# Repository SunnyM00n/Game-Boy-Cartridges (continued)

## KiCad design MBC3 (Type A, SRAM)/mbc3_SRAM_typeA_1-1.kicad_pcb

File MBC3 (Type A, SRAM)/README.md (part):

# Game Boy MBC3 Cartridge - Type A, SRAM

This is an updated design of my flashable MBC3-based cartridge for the Game Boy. The MBC3 mapper improves a lot over the MBC1, and includes a real-time clock for everyone's favorite battery-sucking game.... Mary Kate and Ashley Pocket Planner! Oh, and Pokemon.

**This MBC3 cartridge uses brand new M29F160 EEPROM chips and battery-backed SRAM.**

This circuit board should cover most, if not all, MBC3 games. The features are as follows:

- Able to make games up to 2 MB in size, that use up to 256 Kbit of RAM
- Compatibility with all four of the popular Game Boy battery management ICs - MM1026, MM1134, BA6129, and BA6735
- The option to add battery backup to the cartridge *without* the need of the original battery management ICs
- Fully compatible with both the <a href="https://www.gbxcart.com/">GBxCart RW</a> and sanni's <a href="https://github.com/sanni/cartreader">Open Source Cart Reader (OSCR)</a> so you can transfer games and save files to and from the board

All gerbers and source files can be found in this repo, as this project is fully open source.

## Important Things Before You Start

1) To use this board, you need to have an original Game Boy game that uses an MBC3 mapper chip. <a href="https://catskull.net/gb-rom-database/">You can find a list of games and their mappers here</a>. Use the search function. Please note the RAM is in bytes, not bits. Since SRAM in this repo is defined in bits, you need to convert by multiplying the number of bytes by 8.
2) You will need to remove the MBC3 from your donor cartridge for use on this board. This will require a hot air rework station or a hot plate. There's a list below of other parts you can re-use from the donor cartridge.
3) When soldering parts on, it's a good idea to put kapton tape or otherwise cover the bottom cartridge edge. You do not want to get solder on the cartridge contacts.
4) I am not responsible for any damage you do to your self or your property. Attempt this project at your own risk.
5) I do not guarantee design compatibility. You may encounter issues with certain games. There is also a chance I have made an error in the design or the BOM - if this is the case, I will do everything I can to address the problem as quickly as possible.
6) If you are using this board to make games other than for personal use, you must have permission from the originator to use and distribute any ROM images or other related material. You are responsible for making sure you adhere to any license requirements.

DO NOT use my circuit boards for profiting from stolen work - this especially includes homebrew content, ROM hacks, and using fan-made labels without permission from the originator. **Support original creators!**

## Board Characteristics and Order Information

The zipped folder contains all the gerber files for this board. The following options **must** be chosen when ordering boards for yourself.

- Thickness: 0.8mm
- Surface Finish: ENIG
- Gold Fingers: Yes, 30° chamfer

**I sell this blank circuit board on Etsy, so you don't have to buy a bunch of multiples if you don't want to.** (Click the banner!)

You can use the zipped folder at any board fabricator you like. You may also buy the board from PCBWay using this link (disclosure: I receive 10% of the sale value to go twoards future PCB orders of my own):

<a href="https://oshpark.com/shared_projects/ahA0HcIn">The board is also listed on OSH Park as well.</a> **Be sure to get them in 0.8mm thickness if you order from here.**

## Required Equipment

The EEPROM on the board needs to be programmed somehow. There are a few options for doing this:

1) <a href="https://www.gbxcart.com/">**GBxCart**</a>. This is a perfect option if you want an easy way to make Game Boy cartridges without a lot of extra effort. This is a standalone flasher that plugs into your computer via USB. The cartridge circuit board is fully compatible with it, and it makes reflashing games extremely easy using <a href="https://github.com/lesserkuma/FlashGBX">lesserkuma's FlashGBX software</a>.
2) <a href="https://github.com/sanni/cartreader">**OSCR**</a> by sanni. This is the Open Source Cart Reader, capable of making backups of both the ROM and RAM contents of cartridges across many different systems - like the NES, SNES, Genesis, and of course Game Boy and Game Boy Advance. And you can also use it to flash these Game Boy cartridges. The OSCR however requires assembly (or someone to assemble it for you) and is a bit more cumbersome to interface with on a PC, but it's an extremely powerful tool that I can't recommend enough if you want to expand past Game Boys.
3) At the lowest level, you can buy an EEPROM programmer with a TSOP chip programming adapter. The downside to this method is that you have to desolder the chip every time you want to program it. The <a href="https://flashcatusb.com/">FlashcatUSB</a> is one popular option in retro spaces, but I use the <a href="https://xgecu.myshopify.com/products/xgecu-new-t48-tl866-3gprogrammer-v12-01-support-28000-ics-for-spi-nor-nand-flash-emmc-bga153-162-169-100-221-tsop-sop-plcc">T48 programmer</a> with the <a href="https://xgecu.myshopify.com/products/100-original-xgecu-adp_f48_ex-1-tsop48-special-adapter-for-nor-flash-only-use-on-t48-tl866-3g-programmer">TSOP48 adapter</a>.

## Battery Safety

When assembling a board, I recommend populating all the parts *except* the battery, and getting it to run initially without it. This is to make it easier to fix any solder connections that might need fixing, without having to worry about getting the battery hot. And if you need to rework anything near the battery after you've put it on the board, be safe and remove it before putting a hot soldering iron next to it.

If you're assembling these boards with a hot plate or hot air, *do not* solder the battery on this way. You should use an iron, and keep heat off of the battery as much as possible. 

(Also check polarity!)

## Board Configurations

The board comes with five sets of jumper pads for solder bridges. SJ3, SJ5, and SJ6 require you to solder bridge the middle pad either to the left or right pads. SJ1 and SJ4 are configured by either leaving them alone or bridging them with solder. Here are the situations where you need to add solder bridges.

**<a href="https://github.com/MouseBiteLabs/Game-Boy-Cartridges/wiki/MBC3">You can check out the wiki for some pictures of boards in various configurations to follow along with.</a>**

### Making Games Without SRAM or Battery (SJ1 and SJ4)

Solder bridge SJ1 and SJ4 if your game does not use any SRAM or battery. I don't believe there were ever any MBC3 games made *without* SRAM, but if you wanted to... remove it for some reason, you can.

### MBC3 Type Select (SJ3)

The MBC3 chip you use from the donor cartridge can be one of a few different types:

- If your MBC3 doesn't have a revision letter on it (it just says "MBC3" on it) then bridge the middle pad of SJ3 to the left. (You will also need to populate Q1!)
- If your MBC3 *does* have a revision letter, such as MBC3A or MBC3B, then bridge the middle pad of SJ3 to the right.

*[Images of MBC3 chips from <a href="https://gbhwdb.gekkio.fi/cartridges/mbc3.html">Game Boy Hardware Database</a>.]*

### RAM Size Selection (SJ5 and SJ6, or SW1)

These jumpers are located underneath the MBC3 chip, and labeled "64K" and "256K". Solder them to configure the amount of RAM your cart uses. You must configure these pads for every game you make, unless you do not need RAM. <a href="https://catskull.net/gb-rom-database/">You can find a list of games here with their respective RAM sizes.</a>

- If the game you're making uses 256 Kbit of RAM, then solder the middle pads of the two jumper sets to the right pads.
- If the game you're making uses 64 Kbit of RAM, then solder the middle pads of the two jumper sets to the left pads.
- SJ5 and SJ6 must be soldered in the same direction.
- The footprint of these selection pads should allow for a DPDT switch, part number CAS-220A1, to be placed on these pads instead of having to bridge the pads with solder.

Note that you can make games that only require 64 Kbit of RAM and still use a 256 Kbit SRAM chip. You still need to configure the jumpers to the 64 Kbit setting, though.

### Games Without a Real-Time Clock

If your game does *not* use the RTC function with the crystal X1, then you need to bridge the pads of Z1.

## Test Points and Final Checkout

On the back of the board are five test points. Here's where they are connected:

- TP1: SRAM supply voltage
- TP2: Battery voltage (after R1)
- TP3: Battery voltage (positive terminal of battery)
- TP4: Ground
- TP5: VCC input voltage

After you assemble your game, you should measure the current out of the battery. But first, you should program it with the GBxCart, or if you programmed the EEPROM separately, put it into a Game Boy and cycle power once. Then, flip the PCB upside down on a non-conductive surface (not your leg), and set your multimeter in DC millivolts (or volts). Put the positive probe on TP3 and the negative probe on TP2. If you used a 10kΩ for R1, as indicated in the BOM, you should read a voltage in the single or tens of millivolts for non-RTC games, or up to 40 mV for games using a real-time clock. If you have something much higher, especially voltages above 40mV, then you likely have an issue or short circuit on the board somewhere.

**Note: You need to power up the game at least once before battery currents will make sense - the battery management ICs can start up in an unknown state before applying main power to the board.**

To estimate battery life, see <a href="https://github.com/MouseBiteLabs/Game-Boy-MBC3-Cartridge/tree/main/Technical#estimating-battery-life">this section in the Technical Design Document of my first MBC3 board design</a>, or for more in-depth analysis, <a href="https://hackaday.io/project/11864-tritiled/log/72554-determining-maximum-runtime-176-to-202-years-cr2032">this Hackaday post</a>.

### Current Draw Measurements

The revision of MBC3 chip you are using will influence the current draw out of the battery when the game is off, and thus how long your battery life will last. Using the real-time clock function on the MBC3 will draw more current than if you do not.

For the test set up, I am replacing the battery with a regulated DC power supply set for 3 VDC for consistency, on a cart board with an MM1134 chip for U4, and brand new AS6C62256 SRAM. The "no RTC" measurements have Z1 (or C3) shorted, and the "with RTC" measurements have R2, C2, Z1, and X1 populated. I am using a Fluke 117 Multimeter in DC mV mode for measurements.

| Rev   | P/N      | Current draw (without RTC) | Battery Life Estimate (no RTC, CR2025) | Current draw (with RTC) | Battery Life Estimate (RTC, CR2025)  | Battery Life Estimate (RTC, CR2032) |
| ----- | -------- | -------------------------- | -------------------------------------- | ----------------------- | ------------------------------------ | ----------------------------------- |
| MBC3  | LR385364 |          0.2 uA            |               >50 years                |            1.8 uA       |               10 years               |            14 years                 |
| MBC3  | BU3631K  |          0.6 uA            |                31 years                |            1.6 uA       |               12 years               |            16 years                 |
| MBC3  | P-1      |          0.4 uA            |                47 years                |            3.8 uA       |               5 years                |             7 years                 |
| MBC3A | LR38536B |          0.2 uA            |               >50 years                |            1.5 uA       |               13 years               |            18 years                 |
| MBC3A | BU3632K  |          0.5 uA            |                37 years                |            1.5 uA       |               13 years               |            18 years                 |
| MBC3A | P-2      |          0.5 uA            |                37 years                |            3.9 uA       |               5 years                |            7 years                  |
| MBC3B | BU3634K  |          0.6 uA            |                31 years                |            1.5 uA       |               13 years               |            18 years                 |
| MBC3B | P-2      |          0.4 uA            |                47 years                |            3.7 uA       |               5 years                |            7 years                  |

*Note: The SRAM I used, AS6C62256, drew 0.05 uA by itself for these tests. Your current draw may vary depending on the SRAM you are using.*

## Board Fitment

The shape of this board was originally meant to mimic original Game Boy circuit boards as closely as possible. Unfortunately, when placed in some aftermarket Game Boy cartridge shells (like those from Cloud Game Store), the circuit board has a lot of freedom to rotate around the main screw hole in the bottom-middle of the cartridge. This can cause misalignment when you put it in a Game Boy, which can cause a game to either not load properly (garbled Game Boy logo) or shut off the Game Boy because of a short circuit. This isn't *dangerous* or anything, just annoying.

In order to make the boards fit nicer in any kind of shell, I added extended tabs of circuit board material to the edges of the cartridges to keep it from rotating too much in shells, which was suggested to me by <a href="https://github.com/orangeglo">orangeglo</a>! (Thanks!)

If you're having trouble fitting the circuit board into a shell, because the tabs interfere with the cart edges, you can safely sand or trim them down as there is no copper within the tabs themselves. The only shell that appears to require any kind of trimming are Kitsch-Bent shells.

## Bill of Materials (BOM)

Your parts list will vary depending on the game you are trying to make, and what chips you have for the battery management (if any). **You cannot use both U4 and U5 - you must choose one or the other.** U4 comes from a donor cartridge, and U5 is a readily available aftermarket option.

Please carefully review the parts you need for the board you are trying to make. Do not add any parts to your build that don't appear in the column for the game you are making. This means you *cannot* populate every component on the board at the same time.

**NOTE: If you are *not* using the RTC function of the MBC3, you need to bridge the pads of Z1 (or C3) with solder.**

| Reference Designators | Value/Part Number              | Package          | Description        | No save carts | Save carts with U4 | Save carts without U4 | Source                                           |
| --------------------- | ------------------------------ | ---------------- | ------------------ | ------------- | ------------------ | --------------------- | ------------------------------------------------ |
| B1                    | CR2032, CR2025, CR2016         | CR2032           | Backup Battery     |               | x                  | x                     | [https://mou.sr/3SeAzfT](https://mou.sr/3SeAzfT) |
| C1                    | 0.1uF                          | 0603             | Capacitor (MLCC)   | x             | x                  | x                     | [https://mou.sr/3ENc15O](https://mou.sr/3ENc15O) |
| C2                    | 15pF                           | 0603             | Capacitor (MLCC)   |               | If using RTC       | If using RTC          | https://mou.sr/3PPorjO                           |
| Z1                    | 15pF                           | 0603             | Capacitor (MLCC)   |               | If using RTC       | If using RTC          | https://mou.sr/3PPorjO                           |
| C4                    | 0.1uF                          | 0603             | Capacitor (MLCC)   |               | x                  |                       | [https://mou.sr/3ENc15O](https://mou.sr/3ENc15O) |
| C5                    | 0.1uF                          | 0603             | Capacitor (MLCC)   |               | x                  | x                     | [https://mou.sr/3ENc15O](https://mou.sr/3ENc15O) |
| C6                    | 10uF                           | 0603             | Capacitor (MLCC)   |               | x                  | x                     | [https://mou.sr/3mZtSkF](https://mou.sr/3mZtSkF) |
| C7                    | 0.1uF                          | 0603             | Capacitor (MLCC)   | x             | x                  | x                     | [https://mou.sr/3ENc15O](https://mou.sr/3ENc15O) |
| C8                    | 0.1uF                          | 0603             | Capacitor (MLCC)   |               |                    | x                     | [https://mou.sr/3ENc15O](https://mou.sr/3ENc15O) |
| Q1                    | 2N7002                         | SOT-23           | N-Channel FET      |               | If MBC3 no rev     | x                     | [https://mou.sr/3rgfh6J](https://mou.sr/3rgfh6J) |
| R1                    | 10k                            | 0603             | Resistor           |               | x                  | x                     | [https://mou.sr/3riR7IH](https://mou.sr/3riR7IH) |
| R2                    | 330k                           | 0603             | Resistor           |               | If using RTC       | If using RTC          | [https://mou.sr/3PZ2pvj](https://mou.sr/3PZ2pvj) |
| R9                    | 130k                           | 0603             | Resistor           |               |                    | x                     | [https://mou.sr/3MjXliy](https://mou.sr/3MjXliy) |
| R10                   | 49.9k                          | 0603             | Resistor           |               |                    | x                     | https://mou.sr/3Q3NRZO                           |
| U1                    | M29F160                        | TSOP-48          | Flash EEPROM       | x             | x                  | x                     | [https://mou.sr/3N0a9eL](https://mou.sr/3N0a9eL) |
| U2                    | MBC3                           | QFP-32           | MBC3 Mapper        | x             | x                  | x                     | Donor MBC3 Game Boy cartridge                    |
| U3                    | AS6C6264, AS6C62256            | SOP-28           | SRAM               |               | x                  | x                     | [https://mou.sr/450klcY](https://mou.sr/450klcY) |
| U4                    | MM1026, MM1134, BA6129, BA6735 | SOIC-8           | Battery Management |               | x                  |                       | Donor Game Boy cartridge                         |
| U5                    | TPS3613                        | MSOP-10          | Battery Management |               |                    | x                     | [https://mou.sr/45Ir2kh](https://mou.sr/45Ir2kh) |
| X1                    | 32.768 kHz                     | Radial           | Crystal Oscillator |               | If using RTC       | If using RTC          | https://mou.sr/3ZteKuy                           |

*Note that C9 - C11 footprints are only included on the board for strange edge cases that may require them sometime in the future; do not populate! See the technical design document for more information.*

### Usable Donor Cartridge Parts

You can use a few parts from the donor cart on the new board to save some money. Note that you will generally get better reliability with new parts as opposed to old ones. For example: I have seen failed RAM chips from donors in the past.

1) **C1/Z1, C2, R2, X1: RTC Components** - You can move over these parts if you're using the real-time clock function. The two capacitors are the same value, so they are interchangeable. On games that *don't* use the RTC, you can't move "Z1" over, because it's a resistor on those boards. Also be careful that on my board, the RTC capacitors are designated as "Z1" and "C2" - don't accidentally move the wrong capacitors over from the donor board to these spots!
2) **U2: MBC3** - This one is required
3) **U3: SRAM** - You can use this part *only if* the game you're making uses the same or less amount of RAM that the donor cartridge does
4) **U4: Battery Management IC** - Using this is probably preferred over the TPS3613 because it'll save you money and parts to put on

You could probably transfer over most of the 0.1uF capacitors but they're pretty cheap anyway, so I generally just recommend buying new resistors and capacitors.

## Things to Remember

- The footprint for the battery can fit a CR2032, CR2025, or CR2016 with solder tabs. The only difference is the mAh capacity (larger number = longer life). If you get Panasonic tabbed batteries, you may have to trim the battery tabs to make them fit on the footprint.
  - For untabbed coin cells, you can find battery retainer adapters online, <a href="https://retrogamerepairshop.com/products/hdr-game-boy-game-battery-retainer?variant=40511013290156">like this one</a>.
- For battery management, use either U4 *or* U5 and supporting components. **Do not** use U4 and U5 simultaneously on one board. They will interfere with each other.
- Generally, ROM sizes are conveyed in terms of kilo**bytes** and mega**bytes** (KB, MB). RAM size is usually conveyed in terms of kilo**bits** or mega**bits** (Kbit, Mbit). You can convert Kbit and Mbit to KB and MB by dividing Kbit or Mbit by 8. For example, 256 Kbit = 32 KB.
- You only need to provide ROM and RAM chips that have at least *or greater* the size of the game you are trying to make. That means you can use a 256 Kbit SRAM chip for a game that only requires 64 Kbit of RAM!

## Labels

If you want a Bucket Mouse branded label for your cartridge, look no further than <a href="https://krizdingus.com/mousebitelabs/">krizdingus's designs</a>. Special thanks to Kris for designing these, they look awesome! (If you are going to order/print these, use the high-res images hosted on his website, and *keep the labels for personal or non-commercial use only.*)

## Why Not FRAM?

This particular board is designed for using low retention power SRAM, or Static RAM. One downside to SRAM is that you need a battery to keep the SRAM powered on even when the game is turned off if you want to retain the data on the chip. So eventually the battery will die, and your save data will be lost.

The other popular option for holding save data is using FRAM, or Ferroelectric RAM, to keep save data around even after the battery dies (specifically, the popular part that's used for Game Boy FRAM carts is the FM18W08).

So, why would anyone ever use SRAM over FRAM if FRAM doesn't need a battery? Well, they do come with a number of downsides:

1) Quality, new stock, 5V tolerant FRAM is expensive ($12+ per part at the time of writing).
2) Cheaper FRAM chips from eBay or Aliexpress are notoriously flaky (anecdotally, ~50% success rate).
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
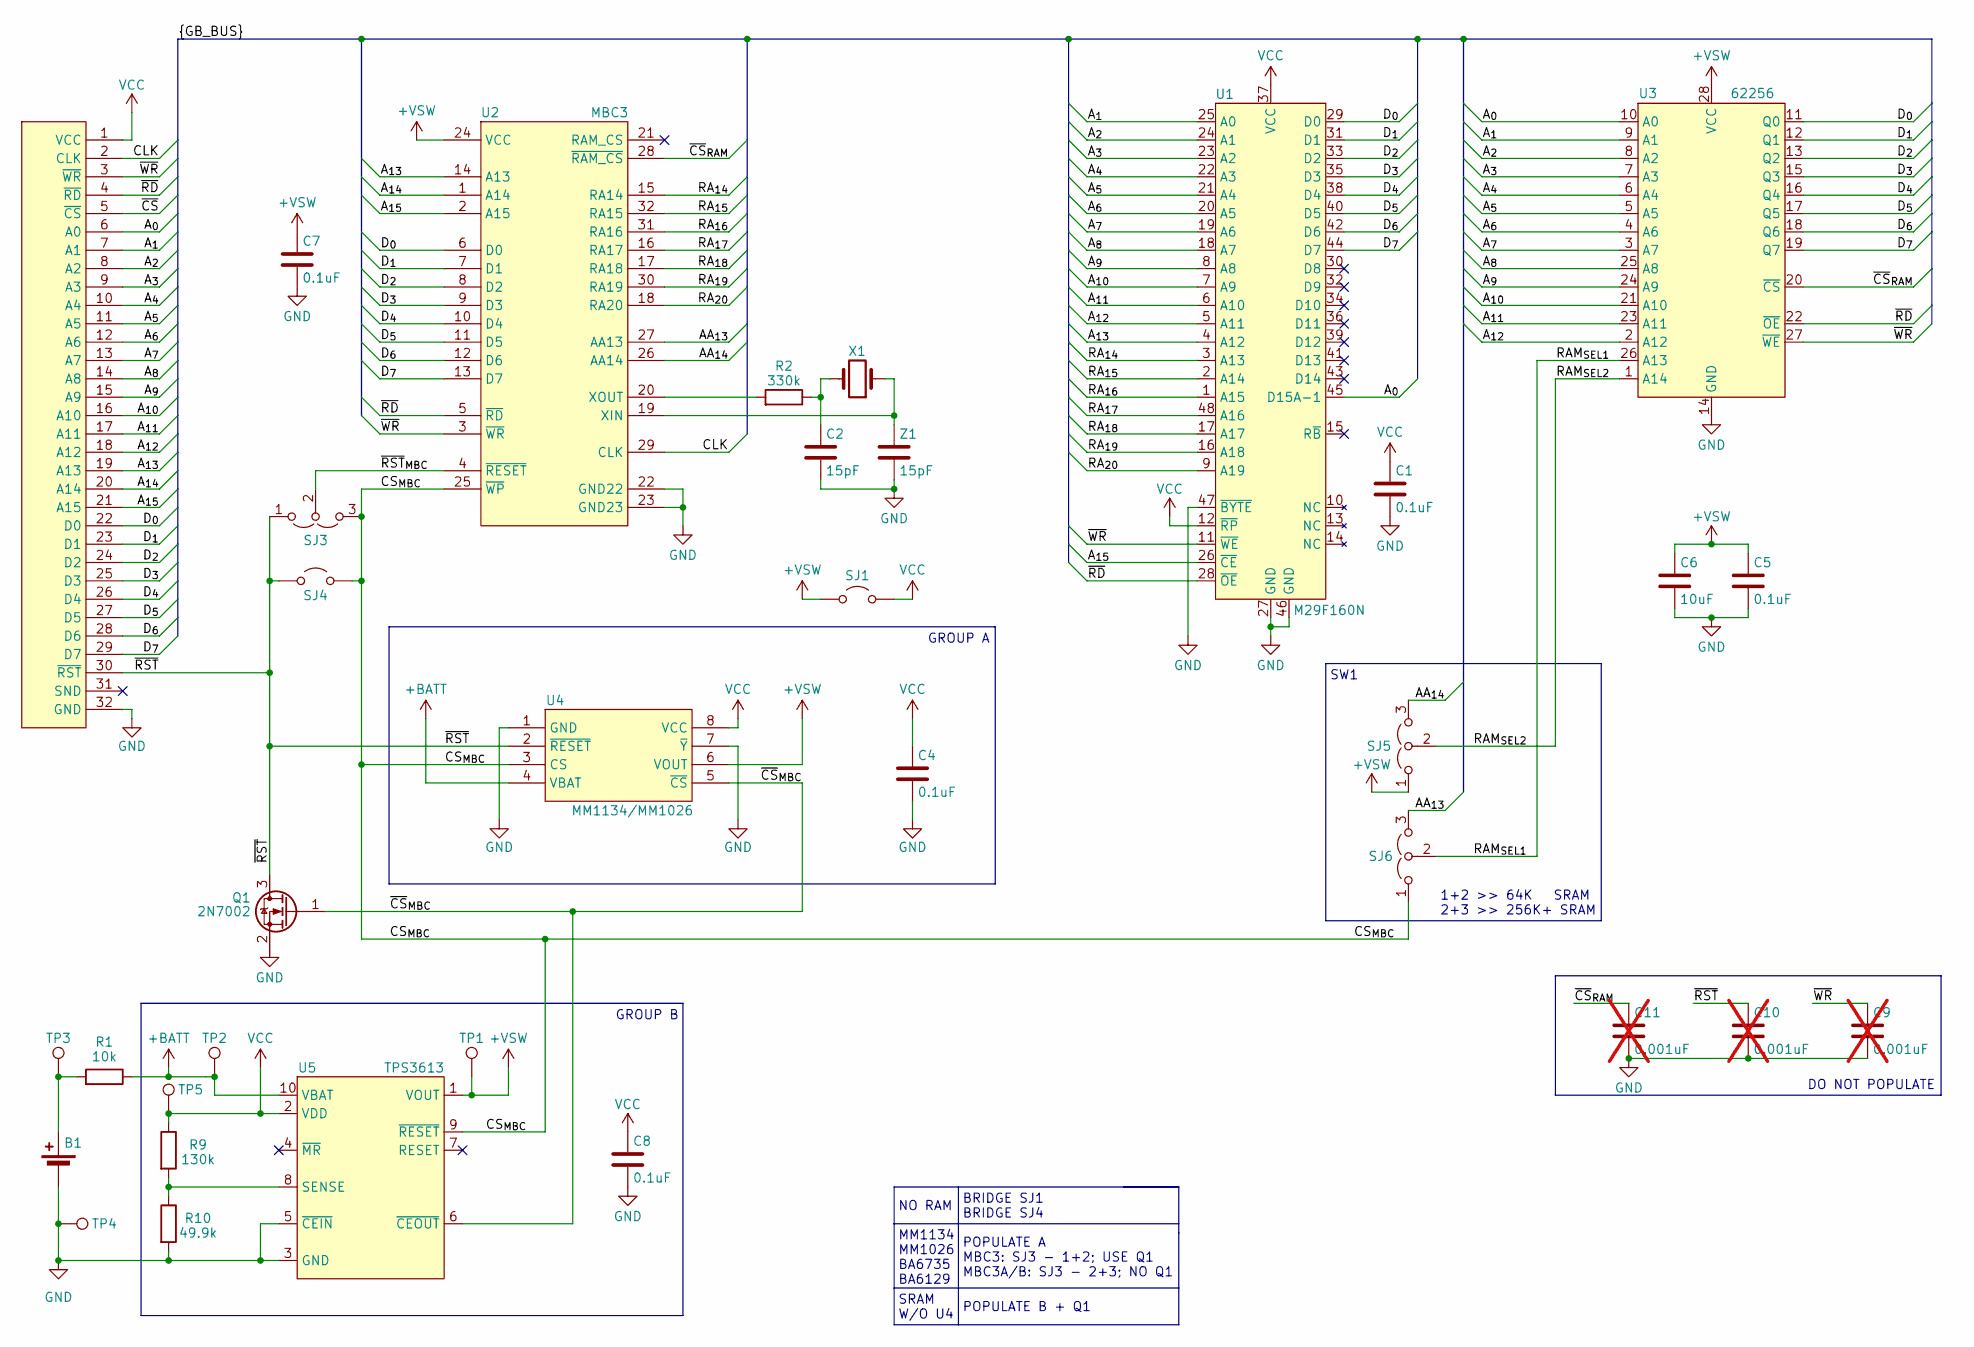
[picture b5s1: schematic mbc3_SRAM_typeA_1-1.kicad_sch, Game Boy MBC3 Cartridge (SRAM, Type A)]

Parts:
B1: CR2025
C1, C4, C5, C7, C8: 0.1uF; C_0603_1608Metric_Boxed
C2: 15pF; C_0603_1608Metric_Boxed
C6: 10uF; C_0603_1608Metric_Boxed
C9, C10, C11: 0.001uF; C_0603_1608Metric_Boxed; not fitted
P2: GBC_CARTTAB; GBC_CART_TABBED
Q1: 2N7002; SOT-23
R1: 10k; R_0603_1608Metric_Boxed
R2: 330k; R_0603_1608Metric_Boxed
R9: 130k; R_0603_1608Metric_Boxed
R10: 49.9k; R_0603_1608Metric_Boxed
SJ1, SJ4: SJ
SJ3, SJ5, SJ6: SJ2W; SJ_2
TP1, TP2, TP3, TP4, TP5: TPB1,27; TestPoint_Pad_D1.0mm
U1: M29F160N; TSOP-I-48_18.4x12mm_P0.5mm
U2: MBC3; QFP-32
U3: 62256; SO28
U4: MM1134/MM1026; SOIC-8_3.9x4.9mm_P1.27mm
U5: TPS3613; MSOP-10_3x3mm_P0.5mm
X1: XTAL-3.2X1.5; XTAL3215
Z1: 15pF; C_0603_1608Metric_Boxed

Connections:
+BATT: R1.1, TP2.1, U4.4 (VBAT), U5.10 (VBAT)
+VSW: C5.1, C6.1, C7.1, SJ1.2 (B), SJ5.1 (A), TP1.1, U2.24 (VCC), U3.28 (VCC), U4.6 (VOUT), U5.1 (VOUT)
/AA_{13}: SJ6.3 (B), U2.27 (AA13)
/AA_{14}: SJ5.3 (B), U2.26 (AA14)
/A_{0}: P2.6 (A0), U1.45 (D15A-1), U3.10 (A0)
/A_{1}: P2.7 (A1), U1.25 (A0), U3.9 (A1)
/A_{2}: P2.8 (A2), U1.24 (A1), U3.8 (A2)
/A_{3}: P2.9 (A3), U1.23 (A2), U3.7 (A3)
/A_{4}: P2.10 (A4), U1.22 (A3), U3.6 (A4)
/A_{5}: P2.11 (A5), U1.21 (A4), U3.5 (A5)
/A_{6}: P2.12 (A6), U1.20 (A5), U3.4 (A6)
/A_{7}: P2.13 (A7), U1.19 (A6), U3.3 (A7)
/A_{8}: P2.14 (A8), U1.18 (A7), U3.25 (A8)
/A_{9}: P2.15 (A9), U1.8 (A8), U3.24 (A9)
/A_{10}: P2.16 (A10), U1.7 (A9), U3.21 (A10)
/A_{11}: P2.17 (A11), U1.6 (A10), U3.23 (A11)
/A_{12}: P2.18 (A12), U1.5 (A11), U3.2 (A12)
/A_{13}: P2.19 (A13), U1.4 (A12), U2.14 (A13)
/A_{14}: P2.20 (A14), U2.1 (A14)
/A_{15}: P2.21 (A15), U1.26 (~CE), U2.2 (A15)
/CLK: P2.2 (CLK), U2.29 (CLK)
/CS_{MBC}: SJ3.3 (B), SJ4.2 (B), SJ6.1 (A), U2.25 (~WP), U4.3 (CS), U5.9 (~RESET)
/D_{0}: P2.22 (D0), U1.29 (D0), U2.6 (D0), U3.11 (Q0)
/D_{1}: P2.23 (D1), U1.31 (D1), U2.7 (D1), U3.12 (Q1)
/D_{2}: P2.24 (D2), U1.33 (D2), U2.8 (D2), U3.13 (Q2)
/D_{3}: P2.25 (D3), U1.35 (D3), U2.9 (D3), U3.15 (Q3)
/D_{4}: P2.26 (D4), U1.38 (D4), U2.10 (D4), U3.16 (Q4)
/D_{5}: P2.27 (D5), U1.40 (D5), U2.11 (D5), U3.17 (Q5)
/D_{6}: P2.28 (D6), U1.42 (D6), U2.12 (D6), U3.18 (Q6)
/D_{7}: P2.29 (D7), U1.44 (D7), U2.13 (D7), U3.19 (Q7)
/RAM_{SEL1}: SJ6.2 (C), U3.26 (A13)
/RAM_{SEL2}: SJ5.2 (C), U3.1 (A14)
/RA_{14}: U1.3 (A13), U2.15 (RA14)
/RA_{15}: U1.2 (A14), U2.32 (RA15)
/RA_{16}: U1.1 (A15), U2.31 (RA16)
/RA_{17}: U1.48 (A16), U2.16 (RA17)
/RA_{18}: U1.17 (A17), U2.17 (RA18)
/RA_{19}: U1.16 (A18), U2.30 (RA19)
/RA_{20}: U1.9 (A19), U2.18 (RA20)
/~CS: P2.5 (~CS)
/~CS_{MBC}: Q1.1 (G), U4.5 (~CS), U5.6 (~CEOUT)
/~CS_{RAM}: C11.1, U2.28 (~RAM_CS), U3.20 (~CS)
/~RD: P2.4 (~RD), U1.28 (~OE), U2.5 (~RD), U3.22 (~OE)
/~RST: C10.1, P2.30 (~RST), Q1.3 (D), SJ3.1 (A), SJ4.1 (A), U4.2 (~RESET)
/~RST_{MBC}: SJ3.2 (C), U2.4 (~RESET)
/~WR: C9.1, P2.3 (~WR), U1.11 (~WE), U2.3 (~WR), U3.27 (~WE)
GND: B1.2 (-), C1.2, C2.2, C4.2, C5.2, C6.2, C7.2, C8.2, C9.2, C10.2, C11.2, P2.32 (GND), Q1.2 (S), R10.2, TP4.1, U1.27 (GND), U1.46 (GND), U1.47 (~BYTE), U2.22 (GND22), U2.23 (GND23), U3.14 (GND), U4.1 (GND), U4.7 (~Y), U5.3 (GND), U5.5 (~CEIN), Z1.2
unnamed: B1.1 (+), R1.2, TP3.1
unnamed: C2.1, R2.1, X1.2
unnamed: U2.19 (XIN), X1.1, Z1.1
unnamed: R2.2, U2.20 (XOUT)
unnamed: R9.2, R10.1, U5.8 (SENSE)
VCC: C1.1, C4.1, C8.1, P2.1 (VCC), R9.1, SJ1.1 (A), TP5.1, U1.12 (~RP), U1.37 (VCC), U4.8 (VCC), U5.2 (VDD)

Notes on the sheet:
MM1134 MM1026 BA6735 BA6129
GROUP A
BRIDGE SJ1 BRIDGE SJ4
NO RAM
POPULATE A MBC3: SJ3 - 1+2; USE Q1 MBC3A/B: SJ3 - 2+3; NO Q1
SRAM W/O U4
DO NOT POPULATE
POPULATE B + Q1
SW1
GROUP B
1+2 >> 64K SRAM 2+3 >> 256K+ SRAM

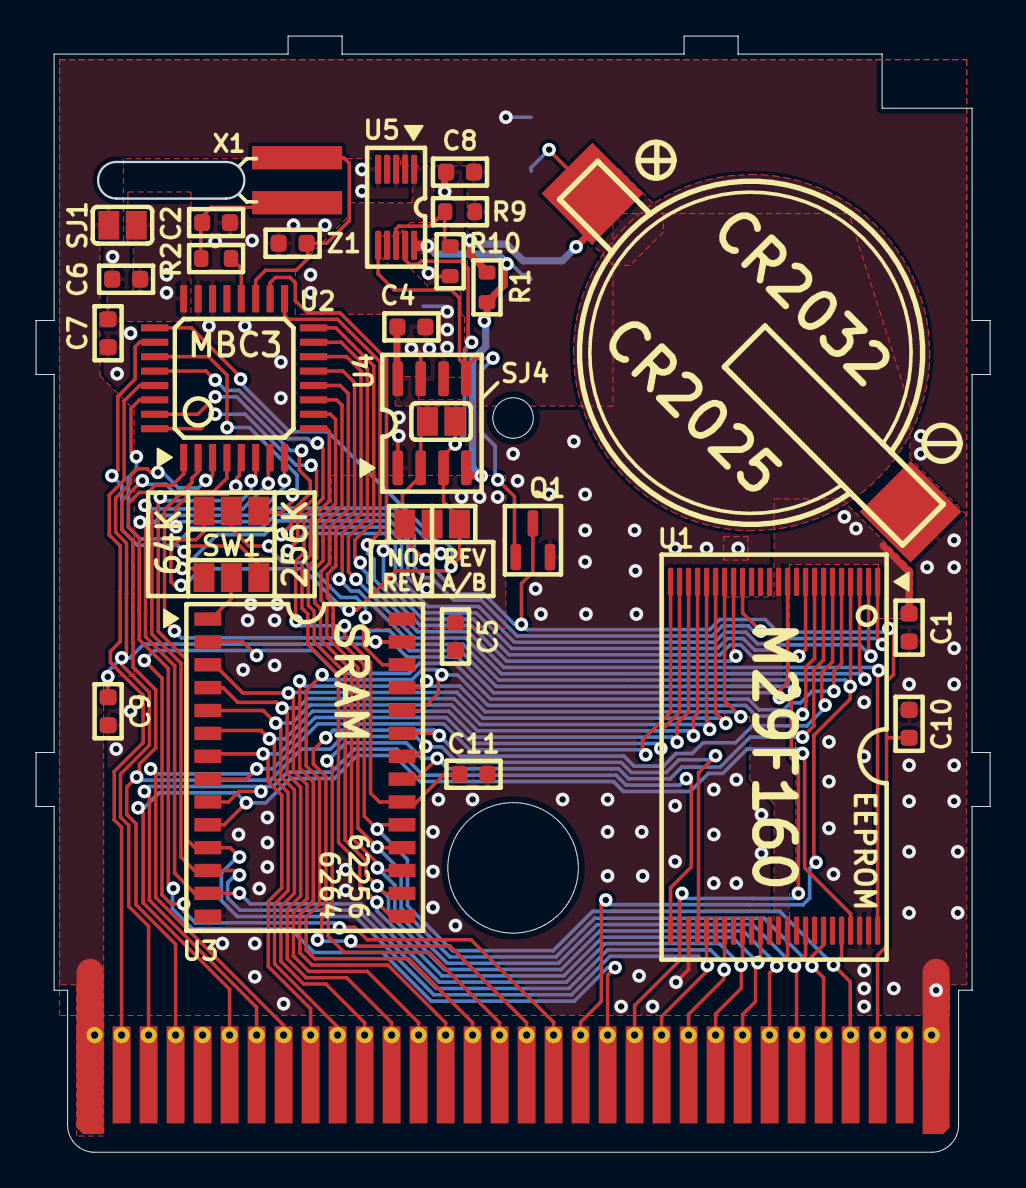
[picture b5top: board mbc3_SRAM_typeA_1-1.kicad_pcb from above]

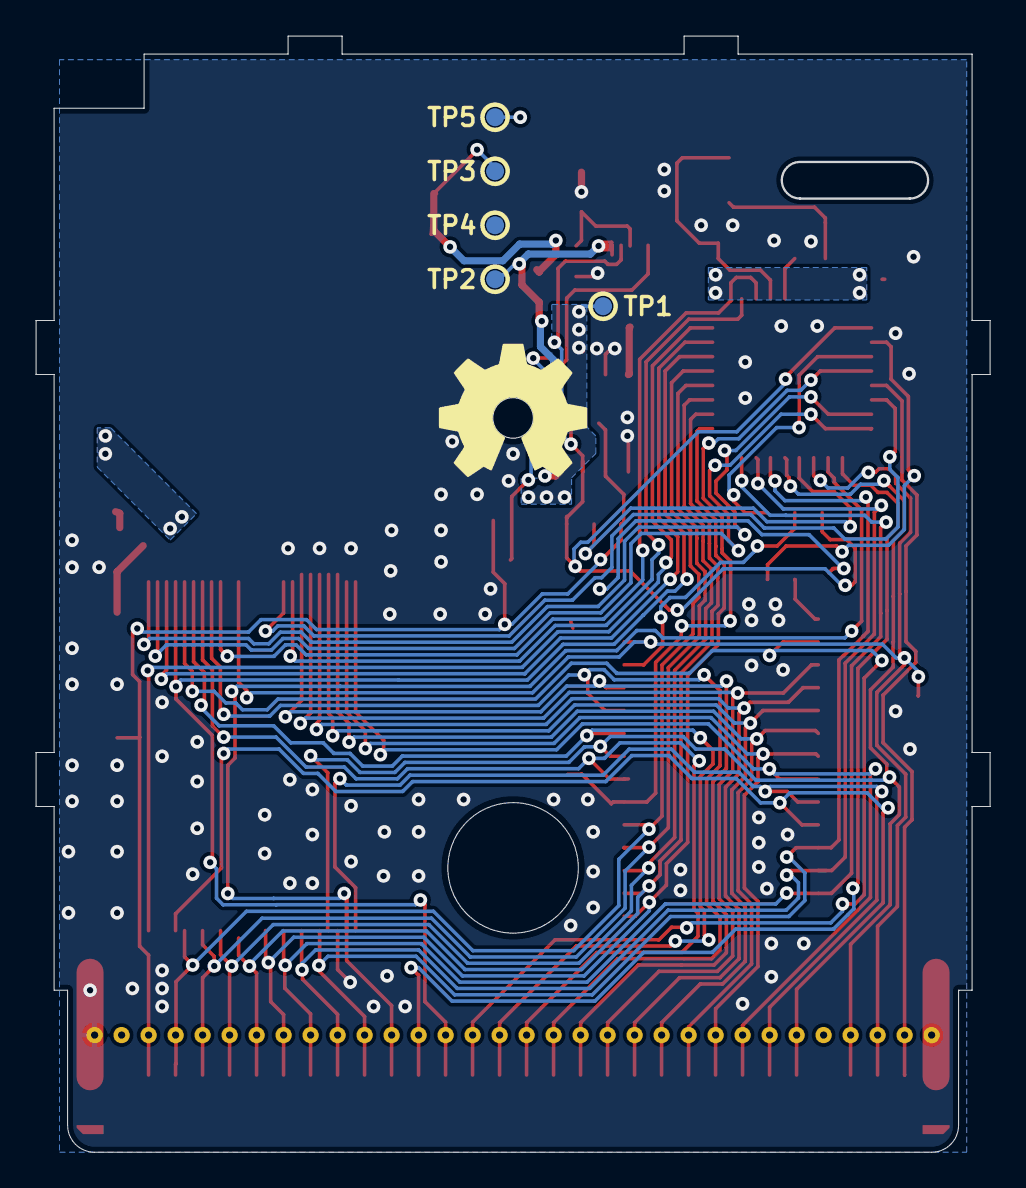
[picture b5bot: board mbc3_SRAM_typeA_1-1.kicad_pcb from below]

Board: 2 copper layers, 53.0 x 62.0 mm, 34 parts (5 on the bottom side), 52 nets.

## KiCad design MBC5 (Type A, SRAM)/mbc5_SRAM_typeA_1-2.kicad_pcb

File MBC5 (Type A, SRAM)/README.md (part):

# Game Boy MBC5 Cartridge - Type A, SRAM

This is an updated design of my flashable MBC5-based cartridge for the Game Boy. The MBC5 mapper greatly augments the memory access of the Game Boy for larger games. Most of the games that came out in the last years of the Game Boy and Game Boy Color used the MBC5 mapper.

**This MBC5 cartridge uses brand new M29F160 EEPROM chips and battery-backed SRAM.**

This circuit board should cover most MBC5 games. The features are as follows:

- Able to make games up to 2 MB in size, that use up to 1 Mbit of RAM
- Compatibility with all four of the popular Game Boy battery management ICs - MM1026, MM1134, BA6129, and BA6735
- The option to add battery backup to the cartridge *without* the need of the original battery management ICs - perfect for MBC5 donors that didn't have batteries in them
- Fully compatible with both the <a href="https://www.gbxcart.com/">GBxCart RW</a> and sanni's <a href="https://github.com/sanni/cartreader">Open Source Cart Reader (OSCR)</a> so you can transfer games and save files to and from the board

All gerbers and source files can be found in this repo, as this project is fully open source **with attribution.**

## Important Things Before You Start

1) To use this board, you need to have an original Game Boy game that uses an MBC5 mapper chip. <a href="https://catskull.net/gb-rom-database/">You can find a list of games and their mappers here</a>. Use the search function. Please note the RAM is in bytes, not bits. Since RAM in this repo is defined in bits, you need to convert by multiplying the number of bytes by 8.
2) You will need to remove the MBC5 from your donor cartridge for use on this board. This will require a hot air rework station or a hot plate. There's a list below of other parts you can re-use from the donor cartridge.
3) When soldering parts on, it's a good idea to put kapton tape or otherwise cover the bottom cartridge edge. You do not want to get solder on the cartridge contacts.
4) I am not responsible for any damage you do to your self or your property. Attempt this project at your own risk.
5) I do not guarantee design compatibility. You may encounter issues with certain games. There is also a chance I have made an error in the design or the BOM - if this is the case, I will do everything I can to address the problem as quickly as possible.
6) If you are using this board to make games other than for personal use, you must have permission from the originator to use and distribute any ROM images or other related material. You are responsible for making sure you adhere to any license requirements.

DO NOT use my circuit boards for profiting from stolen work - this especially includes homebrew content, ROM hacks, and using fan-made labels without permission from the originator. **Support original creators!**

## Board Characteristics and Order Information

The zipped folder contains all the gerber files for this board. The following options **must** be chosen when ordering boards for yourself.

- Thickness: 0.8mm
- Surface Finish: ENIG
- Gold Fingers: Yes, 30° chamfer

**I sell this blank circuit board on Etsy, so you don't have to buy a bunch of multiples if you don't want to.** (Click the banner!)

You can use the zipped folder at any board fabricator you like. You may also buy the board from PCBWay using this link (disclosure: I receive 10% of the sale value to go towards future PCB orders of my own):

<a href="https://oshpark.com/shared_projects/Gdh9uAeD">The board is also listed on OSH Park as well.</a> **Be sure to get them in 0.8mm thickness if you order from here.**

## Required Equipment

The EEPROM on the board needs to be programmed somehow. There are a few options for doing this:

1) <a href="https://www.gbxcart.com/">**GBxCart**</a>. This is a perfect option if you want an easy way to make Game Boy cartridges without a lot of extra effort. This is a standalone flasher that plugs into your computer via USB. The cartridge circuit board is fully compatible with it, and it makes reflashing games extremely easy using <a href="https://github.com/lesserkuma/FlashGBX">lesserkuma's FlashGBX software</a>.
2) <a href="https://github.com/sanni/cartreader">**OSCR**</a> by sanni. This is the Open Source Cart Reader, capable of making backups of both the ROM and RAM contents of cartridges across many different systems - like the NES, SNES, Genesis, and of course Game Boy and Game Boy Advance. And you can also use it to flash these Game Boy cartridges. The OSCR however requires assembly (or someone to assemble it for you) and is a bit more cumbersome to interface with on a PC, but it's an extremely powerful tool that I can't recommend enough if you want to expand past Game Boys.
3) At the lowest level, you can buy an EEPROM programmer with a TSOP chip programming adapter. The downside to this method is that you have to desolder the chip every time you want to program it. The <a href="https://flashcatusb.com/">FlashcatUSB</a> is one popular option in retro spaces, but I use the <a href="https://xgecu.myshopify.com/products/xgecu-new-t48-tl866-3gprogrammer-v12-01-support-28000-ics-for-spi-nor-nand-flash-emmc-bga153-162-169-100-221-tsop-sop-plcc">T48 programmer</a> with the <a href="https://xgecu.myshopify.com/products/100-original-xgecu-adp_f48_ex-1-tsop48-special-adapter-for-nor-flash-only-use-on-t48-tl866-3g-programmer">TSOP48 adapter</a>.

### How to Program the Cartridges

<a href="https://github.com/MouseBiteLabs/Game-Boy-Cartridges/wiki">Check out the wiki for more information.</a>

## Battery Safety

When assembling a board, I recommend populating all the parts *except* the battery, and getting it to run initially without it. This is to make it easier to fix any solder connections that might need fixing, without having to worry about getting the battery hot. And if you need to rework anything near the battery after you've put it on the board, be safe and remove it before putting a hot soldering iron next to it.

If you're assembling these boards with a hot plate or hot air, *do not* solder the battery on this way. You should use an iron, and keep heat off of the battery as much as possible. 

(Also check polarity!)

## Board Configurations

The board comes with three sets of jumper pads for solder bridges. SJ1 and SJ2 require you to solder bridge the middle pad either to the left or right pads. SJ3 is configured by either leaving the pads unsoldered or bridging them with solder. Here are the situations where you need to add solder bridges.

**<a href="https://github.com/MouseBiteLabs/Game-Boy-Cartridges/wiki/MBC5">You can check out the wiki for some pictures of boards in various configurations to follow along with.</a>**

### RAM Size Selection (SJ1 and SJ2, or SW1)

These jumpers are located underneath the MBC5 chip, and labeled "64K" and "256K/1M". Solder them to configure the amount of RAM your cart uses. You must configure these pads for every game you make, unless you do not need RAM. <a href="https://catskull.net/gb-rom-database/">You can find a list of games here with their respective RAM sizes.</a>

- If the game you're making uses 256 Kbit or 1 Mbit of RAM, then solder the middle pads of the two jumper sets to the right pads.
- If the game you're making uses 64 Kbit of RAM, then solder the middle pads of the two jumper sets to the left pads.
- SJ1 and SJ2 must be soldered in the same direction.
- The footprint of these selection pads should allow for a DPDT switch, part number CAS-220A1, to be placed on these pads instead of having to bridge the pads with solder.

Note that you can make games that only require 64 Kbit of RAM and still use a 256 Kbit or 1 Mbit SRAM chip. You still need to configure the jumpers to the 64Kb setting, though.

**I recommend using 64 Kbit or 256 Kbit RAM chips, unless you absolutely need 1 Mbit for the game you are making.**

### Using an MM1134 or BA6735 for U4 (SJ3)

Bridge the jumper SJ3 if you have either an MM1134 or BA6735 for U4, specifically. Any other battery management IC must leave SJ3 unsoldered.

## Test Points and Final Checkout

On the back of the board are five test points. Here's where they are connected:

- TP1: SRAM supply voltage
- TP2: Battery voltage (after R1)
- TP3: Battery voltage (positive terminal of battery)
- TP4: Ground
- TP5: VCC input voltage

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
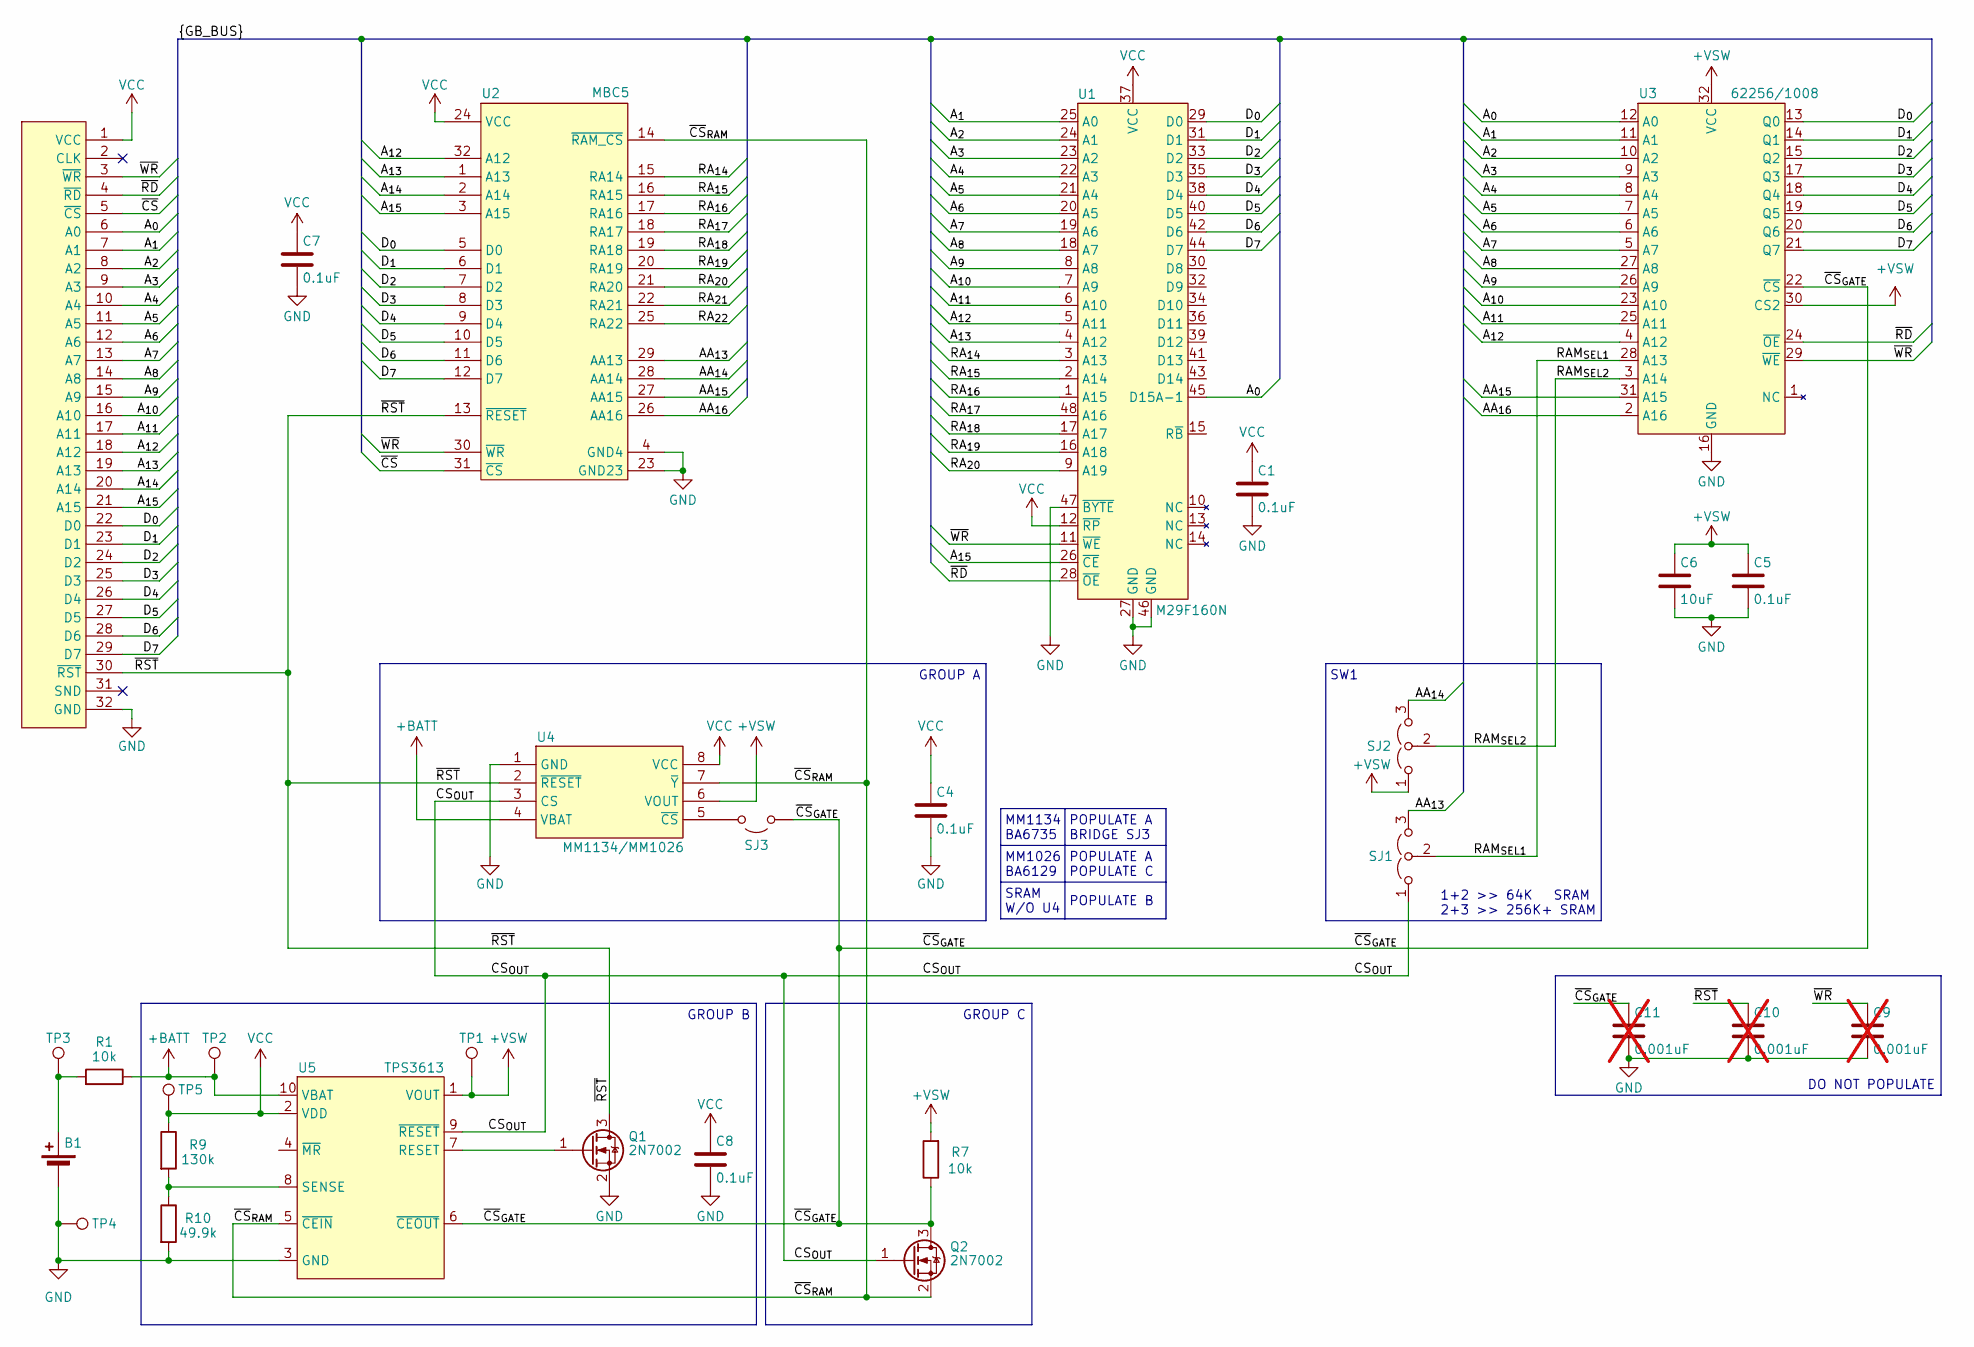
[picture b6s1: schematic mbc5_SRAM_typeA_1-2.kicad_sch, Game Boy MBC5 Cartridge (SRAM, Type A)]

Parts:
B1: CR2025
C1, C4, C5, C7, C8: 0.1uF; C_0603_1608Metric_Boxed
C6: 10uF; C_0603_1608Metric_Boxed
C9, C10, C11: 0.001uF; C_0603_1608Metric_Boxed; not fitted
P1: GBC_CARTTAB; GBC_CART_TABBED
Q1, Q2: 2N7002; SOT-23
R1, R7: 10k; R_0603_1608Metric_Boxed
R9: 130k; R_0603_1608Metric_Boxed
R10: 49.9k; R_0603_1608Metric_Boxed
SJ1, SJ2: SJ2W; SJ_2
SJ3: SJ
TP1, TP2, TP3, TP4, TP5: TPB1,27; TestPoint_Pad_D1.0mm
U1: M29F160N; TSOP-I-48_18.4x12mm_P0.5mm
U2: MBC5; QFP-32
U3: 62256/1008; SO32L_L
U4: MM1134/MM1026; SOIC-8_3.9x4.9mm_P1.27mm
U5: TPS3613; MSOP-10_3x3mm_P0.5mm

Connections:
+BATT: R1.1, TP2.1, U4.4 (VBAT), U5.10 (VBAT)
+VSW: C5.1, C6.1, R7.2, SJ2.1 (A), TP1.1, U3.30 (CS2), U3.32 (VCC), U4.6 (VOUT), U5.1 (VOUT)
/AA_{13}: SJ1.3 (B), U2.29 (AA13)
/AA_{14}: SJ2.3 (B), U2.28 (AA14)
/AA_{15}: U2.27 (AA15), U3.31 (A15)
/AA_{16}: U2.26 (AA16), U3.2 (A16)
/A_{0}: P1.6 (A0), U1.45 (D15A-1), U3.12 (A0)
/A_{1}: P1.7 (A1), U1.25 (A0), U3.11 (A1)
/A_{2}: P1.8 (A2), U1.24 (A1), U3.10 (A2)
/A_{3}: P1.9 (A3), U1.23 (A2), U3.9 (A3)
/A_{4}: P1.10 (A4), U1.22 (A3), U3.8 (A4)
/A_{5}: P1.11 (A5), U1.21 (A4), U3.7 (A5)
/A_{6}: P1.12 (A6), U1.20 (A5), U3.6 (A6)
/A_{7}: P1.13 (A7), U1.19 (A6), U3.5 (A7)
/A_{8}: P1.14 (A8), U1.18 (A7), U3.27 (A8)
/A_{9}: P1.15 (A9), U1.8 (A8), U3.26 (A9)
/A_{10}: P1.16 (A10), U1.7 (A9), U3.23 (A10)
/A_{11}: P1.17 (A11), U1.6 (A10), U3.25 (A11)
/A_{12}: P1.18 (A12), U1.5 (A11), U2.32 (A12), U3.4 (A12)
/A_{13}: P1.19 (A13), U1.4 (A12), U2.1 (A13)
/A_{14}: P1.20 (A14), U2.2 (A14)
/A_{15}: P1.21 (A15), U1.26 (~CE), U2.3 (A15)
/CS_{OUT}: Q2.1 (G), SJ1.1 (A), U4.3 (CS), U5.9 (~RESET)
/D_{0}: P1.22 (D0), U1.29 (D0), U2.5 (D0), U3.13 (Q0)
/D_{1}: P1.23 (D1), U1.31 (D1), U2.6 (D1), U3.14 (Q1)
/D_{2}: P1.24 (D2), U1.33 (D2), U2.7 (D2), U3.15 (Q2)
/D_{3}: P1.25 (D3), U1.35 (D3), U2.8 (D3), U3.17 (Q3)
/D_{4}: P1.26 (D4), U1.38 (D4), U2.9 (D4), U3.18 (Q4)
/D_{5}: P1.27 (D5), U1.40 (D5), U2.10 (D5), U3.19 (Q5)
/D_{6}: P1.28 (D6), U1.42 (D6), U2.11 (D6), U3.20 (Q6)
/D_{7}: P1.29 (D7), U1.44 (D7), U2.12 (D7), U3.21 (Q7)
/RAM_{SEL1}: SJ1.2 (C), U3.28 (A13)
/RAM_{SEL2}: SJ2.2 (C), U3.3 (A14)
/RA_{14}: U1.3 (A13), U2.15 (RA14)
/RA_{15}: U1.2 (A14), U2.16 (RA15)
/RA_{16}: U1.1 (A15), U2.17 (RA16)
/RA_{17}: U1.48 (A16), U2.18 (RA17)
/RA_{18}: U1.17 (A17), U2.19 (RA18)
/RA_{19}: U1.16 (A18), U2.20 (RA19)
/RA_{20}: U1.9 (A19), U2.21 (RA20)
/RA_{21}: U2.22 (RA21)
/RA_{22}: U2.25 (RA22)
/~CS: P1.5 (~CS), U2.31 (~CS)
/~CS_{GATE}: C11.1, Q2.3 (D), R7.1, SJ3.2 (B), U3.22 (~CS), U5.6 (~CEOUT)
/~CS_{RAM}: Q2.2 (S), U2.14 (~RAM_CS), U4.7 (~Y), U5.5 (~CEIN)
/~RD: P1.4 (~RD), U1.28 (~OE), U3.24 (~OE)
/~RST: C10.1, P1.30 (~RST), Q1.3 (D), U2.13 (~RESET), U4.2 (~RESET)
/~WR: C9.1, P1.3 (~WR), U1.11 (~WE), U2.30 (~WR), U3.29 (~WE)
GND: B1.2 (-), C1.2, C4.2, C5.2, C6.2, C7.2, C8.2, C9.2, C10.2, C11.2, P1.32 (GND), Q1.2 (S), R10.2, TP4.1, U1.27 (GND), U1.46 (GND), U1.47 (~BYTE), U2.4 (GND4), U2.23 (GND23), U3.16 (GND), U4.1 (GND), U5.3 (GND)
unnamed: B1.1 (+), R1.2, TP3.1
unnamed: Q1.1 (G), U5.7 (RESET)
unnamed: SJ3.1 (A), U4.5 (~CS)
unnamed: R9.2, R10.1, U5.8 (SENSE)
VCC: C1.1, C4.1, C7.1, C8.1, P1.1 (VCC), R9.1, TP5.1, U1.12 (~RP), U1.37 (VCC), U2.24 (VCC), U4.8 (VCC), U5.2 (VDD)

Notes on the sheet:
POPULATE A BRIDGE SJ3
GROUP C
MM1134 BA6735
GROUP A
SW1
1+2 >> 64K SRAM 2+3 >> 256K+ SRAM
MM1026 BA6129
GROUP B
SRAM W/O U4
DO NOT POPULATE
POPULATE B
POPULATE A POPULATE C

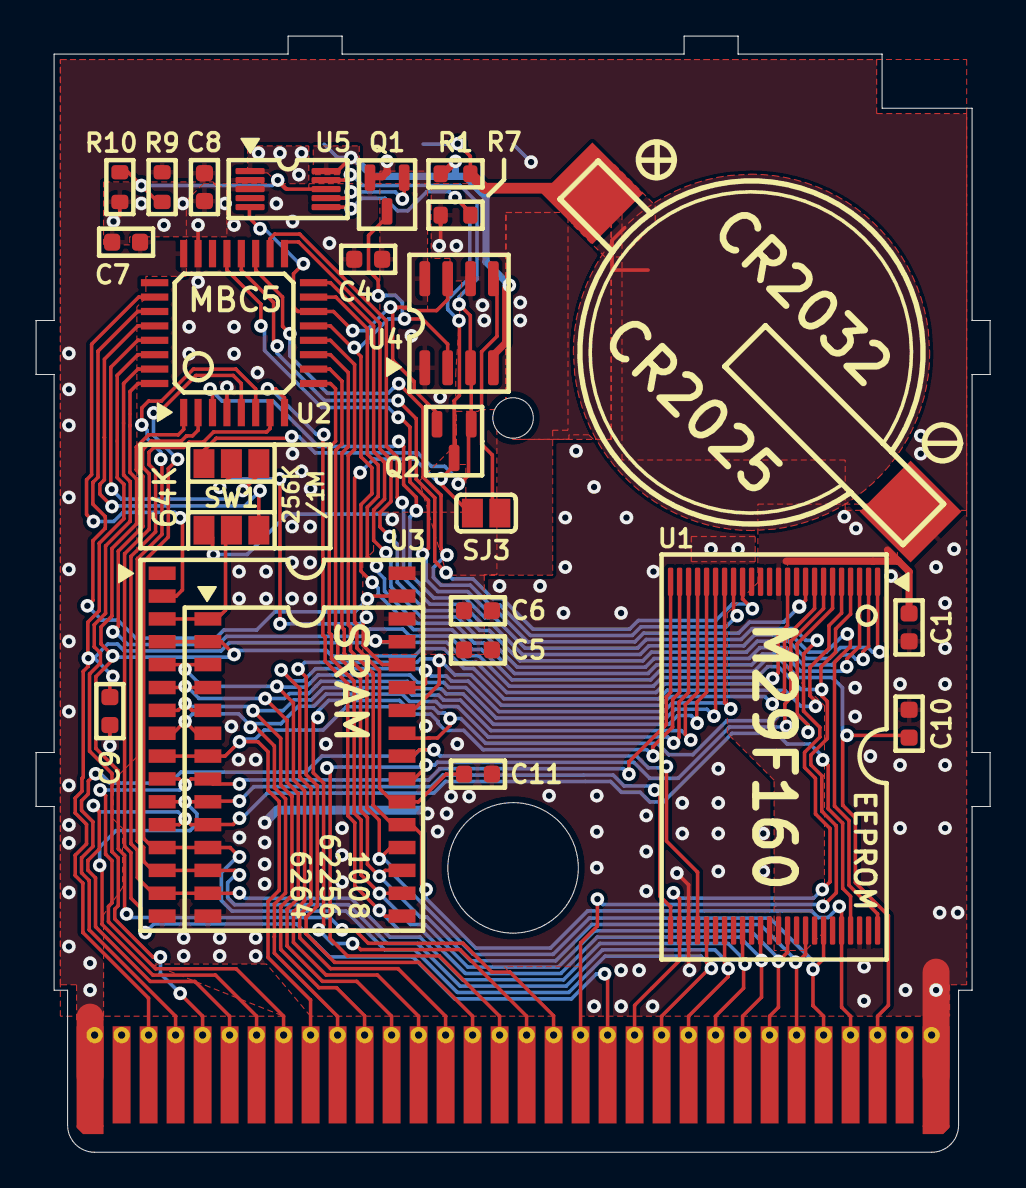
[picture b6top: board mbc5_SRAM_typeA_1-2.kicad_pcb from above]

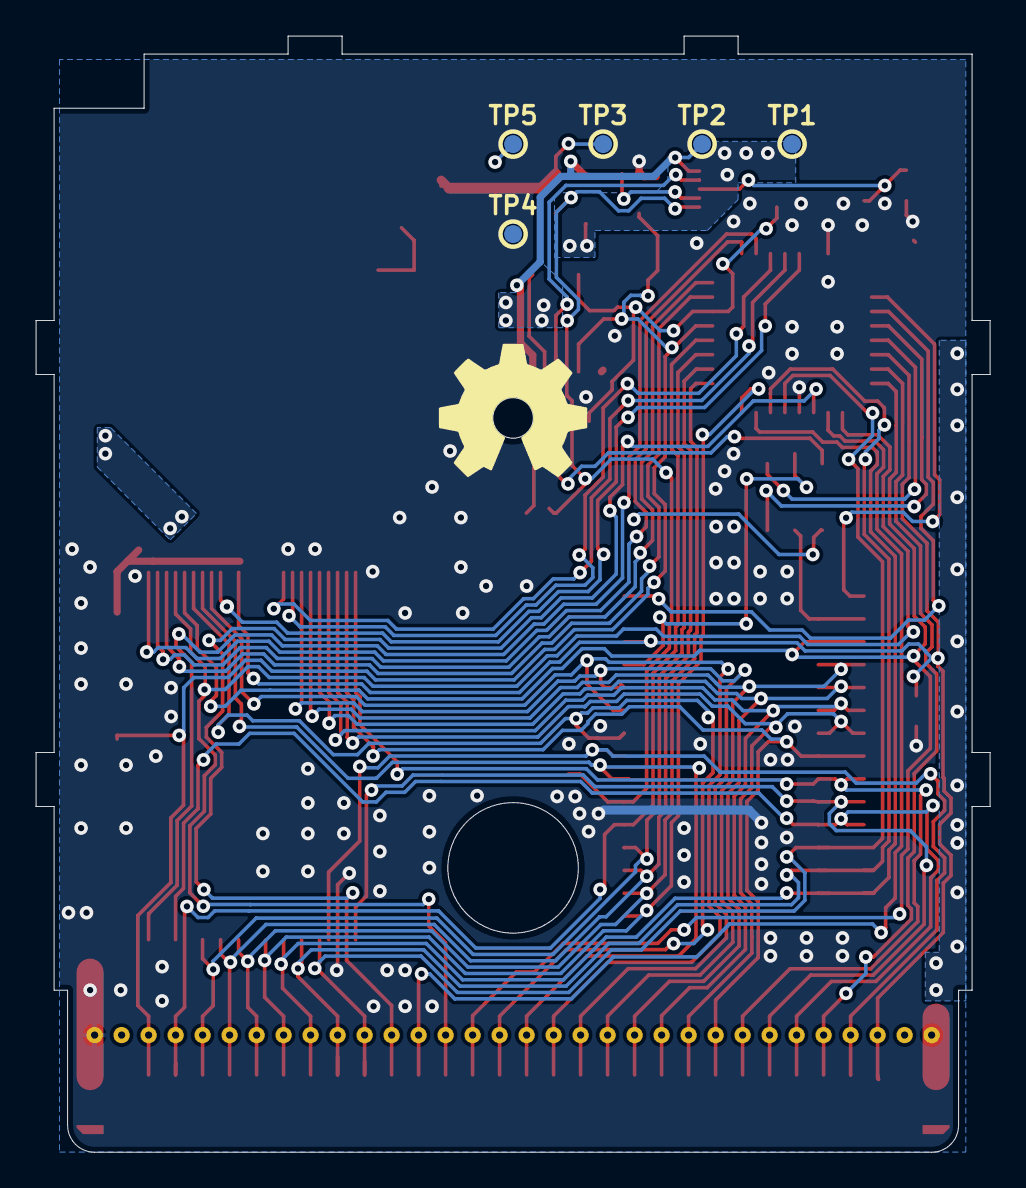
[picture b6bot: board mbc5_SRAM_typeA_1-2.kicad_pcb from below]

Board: 2 copper layers, 53.0 x 62.0 mm, 30 parts (5 on the bottom side), 52 nets.

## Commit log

2025-05-03 Fix MBC5 reference
